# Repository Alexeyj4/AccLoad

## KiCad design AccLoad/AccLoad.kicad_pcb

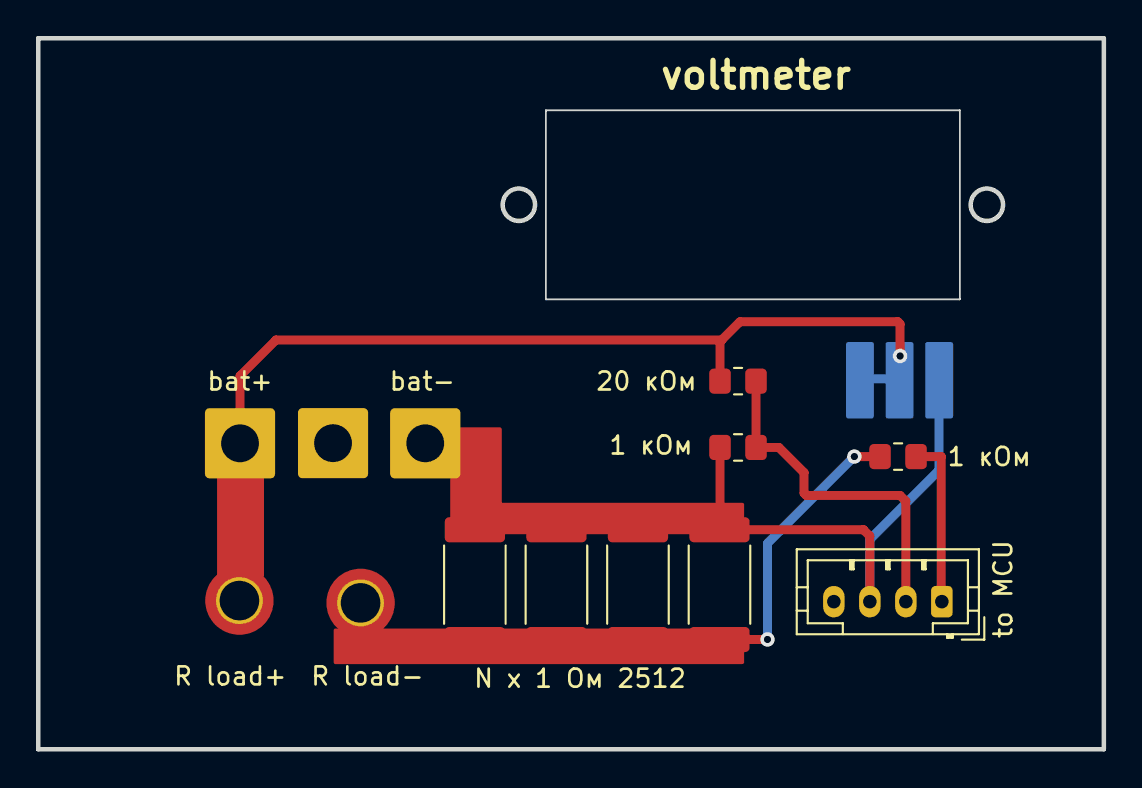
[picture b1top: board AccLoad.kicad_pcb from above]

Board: 2 copper layers, 59.2 x 39.5 mm, 15 parts (0 on the bottom side), 5 nets.

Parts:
H1: bat+; SolderWire-1.5sqmm_1x01_D1.7mm_OD3.9mm
H2: bat-; SolderWire-1.5sqmm_1x01_D1.7mm_OD3.9mm
H3: v+; APEX_voltmeter_pin
H4: v-; APEX_voltmeter_pin
H5: R load+; MountingHole_2.2mm_M2_DIN965_Pad_TopBottom
H6: R load-; MountingHole_2.2mm_M2_DIN965_Pad_TopBottom
H nu: nu; SolderWire-1.5sqmm_1x01_D1.7mm_OD3.9mm
J1: to MCU; JST_PH_B4B-PH-K_1x04_P2.00mm_Vertical
R1: N x 1 Ом 2512; R_2512_6332Metric_Pad1.40x3.35mm_HandSolder
R2, R3, R4: 1 Ом 1 Вт; R_2512_6332Metric_Pad1.40x3.35mm_HandSolder
R9: 20 кОм; R_0805_2012Metric_Pad1.20x1.40mm_HandSolder
R10, R11: 1 кОм; R_0805_2012Metric_Pad1.20x1.40mm_HandSolder

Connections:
unnamed: H6.1, R1.2, R2.2, R3.2, R4.2, R11.1
bat1+: H1.1, H3.1, H5.1, R9.1
bat1-: H2.1, H4.1, J1.3, R1.1, R2.1, R3.1, R4.1, R10.2
i1: J1.1, R11.2
u1: J1.2, R9.2, R10.1

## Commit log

2023-03-28 ino released
2023-03-28 beta
2023-03-29 to production
2023-03-30 fixed bug winh 10 min interval
2023-03-30 exe exported
2023-03-31 added charts drawing
2023-04-01 fixed buf with a-h norma measure
2023-04-01 fixed bug with reset canvas
2023-04-01 fixed bug with canvas cpu (memory) leakage
2023-04-03 fixed error with a-h norma
2023-04-10 added res to Ipin
2023-04-18 star PCB designing
2023-04-18 changed b2b
2023-04-21 fixed errors
2023-04-25 PCD maked
2023-04-26 fixed PCB error with voltmeter+- and border reroute
2023-05-04 fixed error in PCB with voltmeter
